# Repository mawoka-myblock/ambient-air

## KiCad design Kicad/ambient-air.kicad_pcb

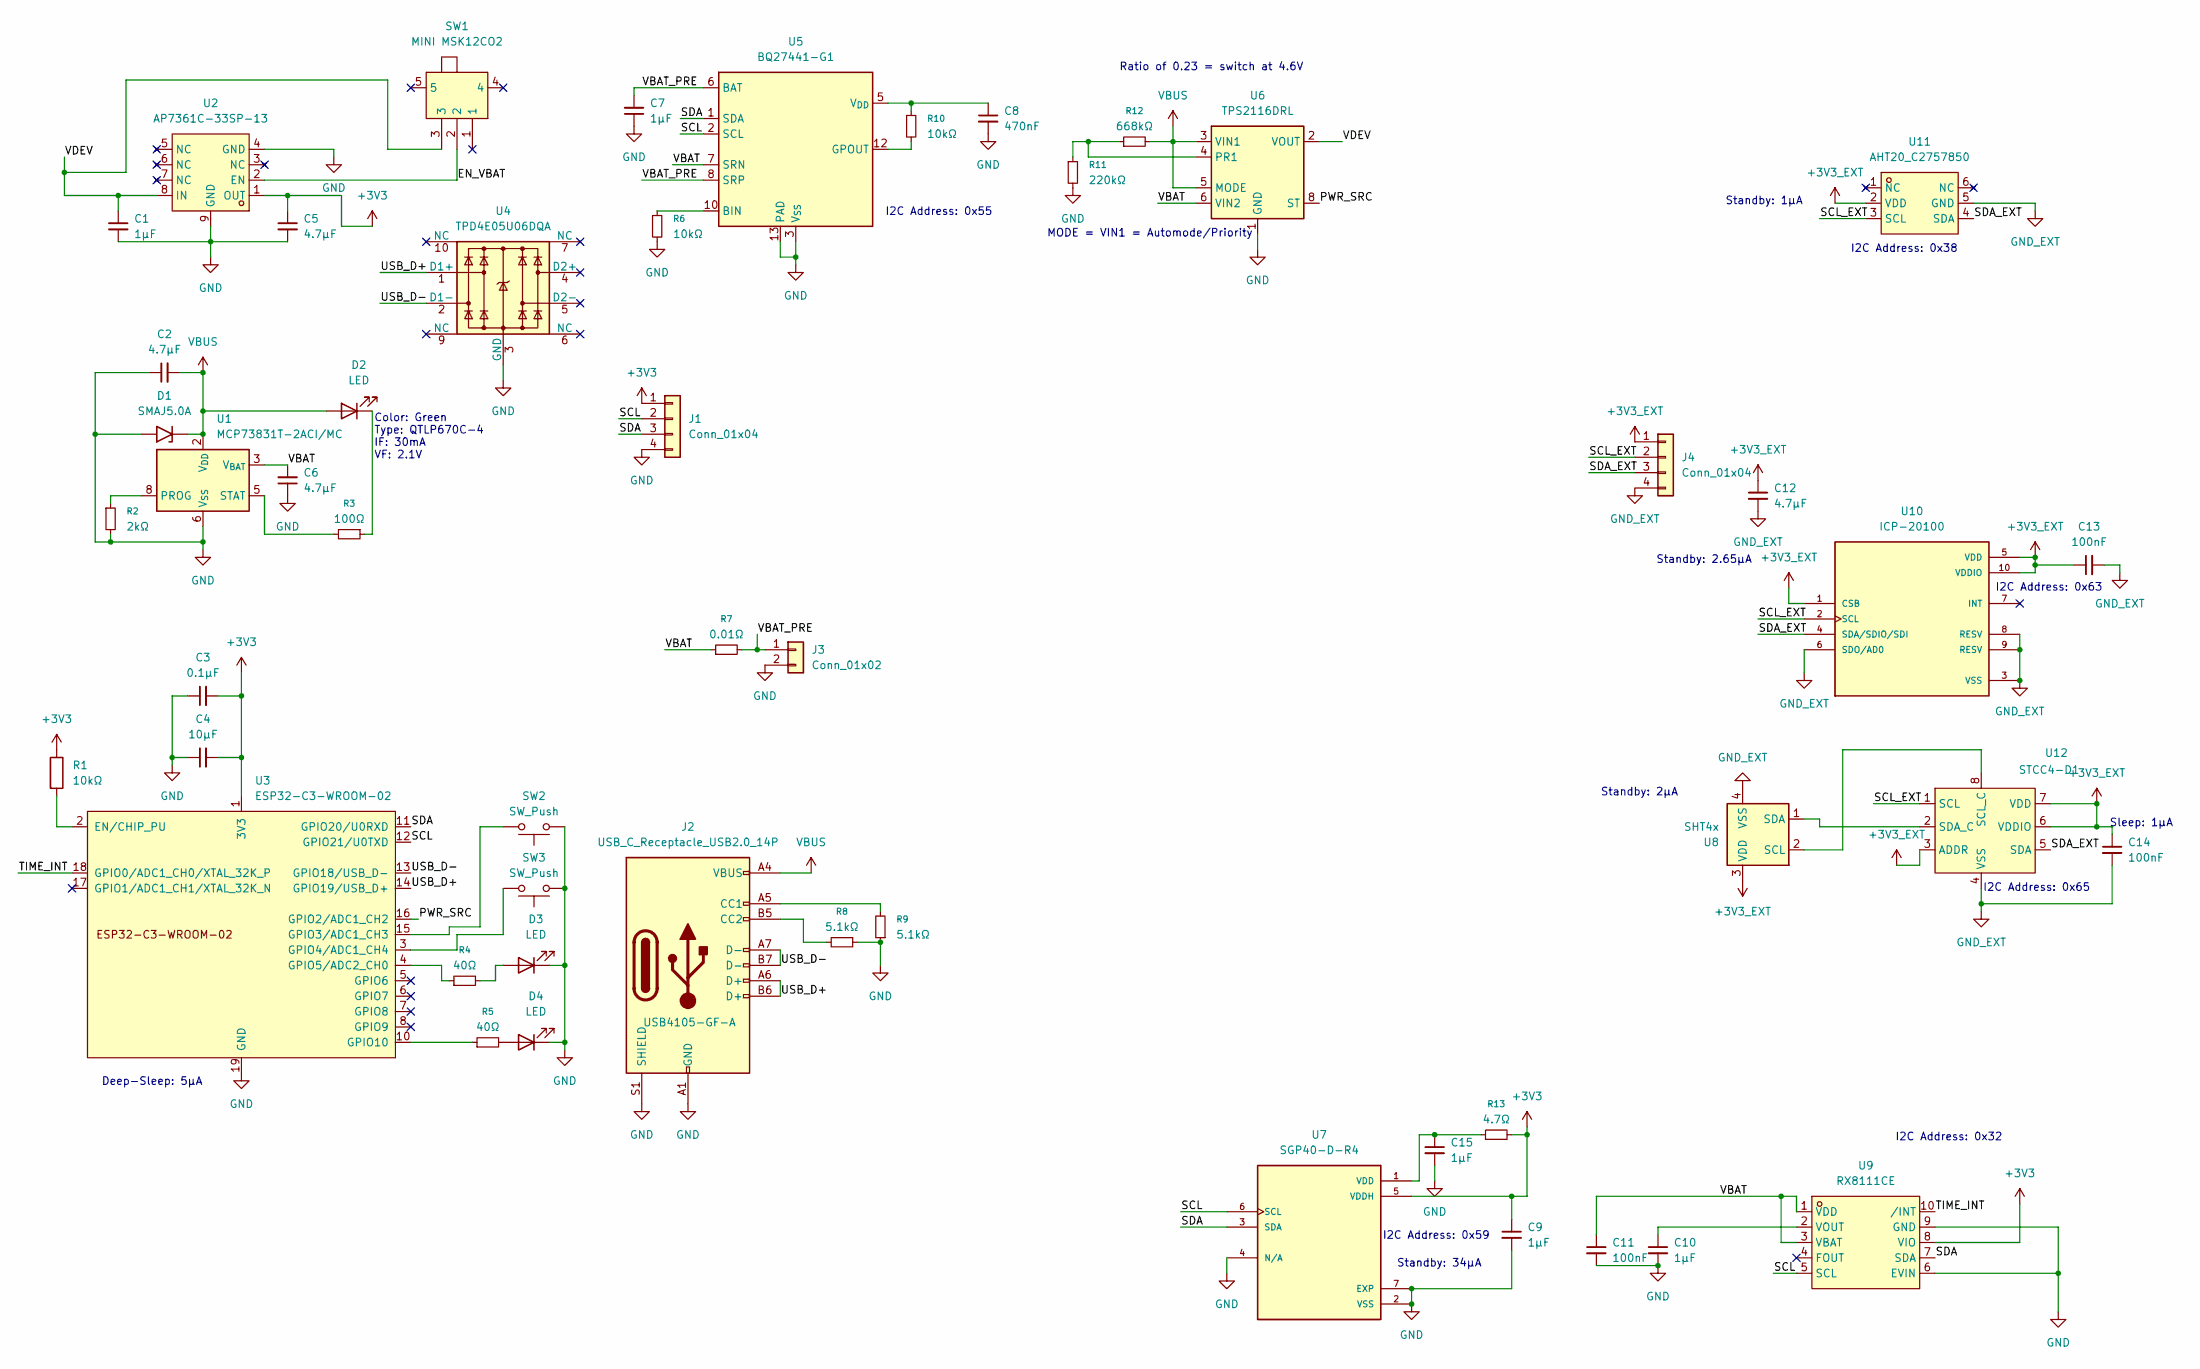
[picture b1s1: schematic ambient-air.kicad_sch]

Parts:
C1, C7, C9, C10, C15: 1µF; C_0603_1608Metric
C2, C5, C6, C12: 4.7µF; C_0805_2012Metric
C3: 0.1µF; C_0805_2012Metric
C4: 10µF; C_0805_2012Metric
C8: 470nF; C_0805_2012Metric
C11, C13, C14: 100nF; C_0805_2012Metric
D1: SMAJ5.0A; D_SMA
D2, D3, D4: LED; CP_EIA-3528-12_Kemet-T
J1, J4: Conn_01x04; JST_SH_SM04B-SRSS-TB_1x04-1MP_P1.00mm_Horizontal
J2: USB_C_Receptacle_USB2.0_14P; USB_C_Receptacle_GCT_USB4105-xx-A_16P_TopMnt_Horizontal
J3: Conn_01x02; JST_PH_S2B-PH-SM4-TB_1x02-1MP_P2.00mm_Horizontal
R1, R6, R10: 10kΩ; R_0805_2012Metric
R2: 2kΩ; R_0805_2012Metric
R3: 100Ω; R_0603_1608Metric
R4, R5: 40Ω; R_0603_1608Metric
R7: 0.01Ω; R_0805_2012Metric
R8, R9: 5.1kΩ; R_0805_2012Metric
R11: 220kΩ; R_0603_1608Metric
R12: 668kΩ; R_0603_1608Metric
R13: 4.7Ω; R_0603_1608Metric
SW1: MINI MSK12CO2; SW-SMD_MSK12CO2; LCSC Part C2681570
SW2, SW3: SW_Push; SW-SMD_L6.0-W3.5-LS8.2
U1: MCP73831T-2ACI/MC; DFN-8-1EP_3x2mm_P0.5mm_EP1.7x1.4mm
U2: AP7361C-33SP-13; ESOP-8_L4.9-W3.9-P1.27-LS6.0-BL-EP; LCSC Part C4943338
U3: ESP32-C3-WROOM-02
U4: TPD4E05U06DQA; USON-10_2.5x1.0mm_P0.5mm
U5: BQ27441-G1; Texas_S-PDSO-N12
U6: TPS2116DRL; SOT-583-8
U7: SGP40-D-R4; XCDR_SGP40-D-R4; PARTREV 1.2
U8: SHT4x; Sensirion_DFN-4_1.5x1.5mm_P0.8mm_SHT4x_NoCentralPad
U9: RX8111CE; OSC-SMD_10P-L3.2-W2.5-BL-1; MPN RX8111CE B; LCSC Part C2929261
U10: ICP-20100; PQFN50P200X200X85-10N; PARTREV 1.1
U11: AHT20_C2757850; SENSOR-SMD_L3.0-W3.0-P1.00-BR; LCSC Part C2757850
U12: STCC4-D1; STCC4DR3

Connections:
+3V3: C3.2, C4.2, C5.1, C9.1, J1.1, R1.1, R13.2, U2.1 (OUT), U3.1 (3V3), U7.5 (VDDH), U9.8 (VIO)
+3V3_EXT: C12.1, C13.1, C14.1, J4.1, U8.3 (VDD), U10.1 (CSB), U10.5 (VDD), U10.10 (VDDIO), U11.2 (VDD), U12.3 (ADDR), U12.6 (VDDIO), U12.7 (VDD)
/EN_VBAT: SW1.2, U2.2 (EN)
/PWR_SRC: U3.16 (GPIO2/ADC1_CH2), U6.8 (ST)
/SCL: J1.2, U3.12 (GPIO21/U0TXD), U5.2 (SCL), U7.6 (SCL), U9.5 (SCL)
/SCL_EXT: J4.2, U10.2 (SCL), U11.3 (SCL), U12.1 (SCL)
/SDA: J1.3, U3.11 (GPIO20/U0RXD), U5.1 (SDA), U7.3 (SDA), U9.7 (SDA)
/SDA_EXT: J4.3, U10.4 (SDA/SDIO/SDI), U11.4 (SDA), U12.5 (SDA)
/TIME_INT: U3.18 (GPIO0/ADC1_CH0/XTAL_32K_P), U9.10 (/INT)
/USB_D+: J2.A6 (D+), J2.B6 (D+), U3.14 (GPIO19/USB_D+), U4.1 (D1+)
/USB_D-: J2.A7 (D-), J2.B7 (D-), U3.13 (GPIO18/USB_D-), U4.2 (D1-)
/VBAT: C6.2, C11.1, R7.1, U1.3 (V_{BAT}), U1.4 (V_{BAT}), U5.7 (SRN), U6.6 (VIN2), U9.1 (VDD), U9.3 (VBAT)
/VBAT_PRE: C7.2, J3.1, R7.2, U5.6 (BAT), U5.8 (SRP)
/VDEV: C1.1, SW1.3, U2.8 (IN), U6.2 (VOUT), U6.7 (VOUT)
GND: C1.2, C2.1, C3.1, C4.1, C5.2, C6.1, C7.1, C8.2, C9.2, C10.2, C11.2, C15.2, D1.2 (A2), D3.1 (K), D4.1 (K), J1.4, J2.A1 (GND), J2.A12 (GND), J2.B1 (GND), J2.B12 (GND), J2.S1 (SHIELD), J3.2, R2.2, R6.2, R8.1, R9.1, R11.2, SW2.1, SW3.1, U1.6 (V_{SS}), U2.4 (GND), U2.9 (GND), U3.9 (GND), U3.19 (GND), U4.3 (GND), U4.8 (GND), U5.3 (V_{SS}), U5.13 (PAD), U6.1 (GND), U7.2 (VSS), U7.4 (N/A), U7.7 (EXP), U9.6 (EVIN), U9.9 (GND)
GND_EXT: C12.2, C13.2, C14.2, J4.4, U8.4 (VSS), U10.3 (VSS), U10.6 (SDO/AD0), U10.8 (RESV), U10.9 (RESV), U11.5 (GND), U12.4 (VSS)
unnamed: D2.1 (K), R3.1
unnamed: D3.2 (A), R4.2
unnamed: D4.2 (A), R5.2
unnamed: J2.A5 (CC1), R9.2
unnamed: J2.B5 (CC2), R8.2
unnamed: R2.1, U1.8 (PROG)
unnamed: R3.2, U1.5 (STAT)
unnamed: R1.2, U3.2 (EN/CHIP_PU)
unnamed: SW2.2, U3.15 (GPIO3/ADC1_CH3)
unnamed: SW3.2, U3.3 (GPIO4/ADC1_CH4)
unnamed: R4.1, U3.4 (GPIO5/ADC2_CH0)
unnamed: R5.1, U3.10 (GPIO10)
unnamed: R6.1, U5.10 (BIN)
unnamed: R10.2, U5.12 (GPOUT)
unnamed: C8.1, R10.1, U5.5 (V_{DD})
unnamed: R11.1, R12.1, U6.4 (PR1)
unnamed: C15.1, R13.1, U7.1 (VDD)
unnamed: C10.1, U9.2 (VOUT)
unnamed: U8.2 (SCL), U12.8 (SCL_C)
unnamed: U8.1 (SDA), U12.2 (SDA_C)
VBUS: C2.2, D1.1 (A1), D2.2 (A), J2.A4 (VBUS), J2.A9 (VBUS), J2.B4 (VBUS), J2.B9 (VBUS), R12.2, U1.1 (V_{DD}), U1.2 (V_{DD}), U6.3 (VIN1), U6.5 (MODE)

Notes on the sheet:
Deep-Sleep: 5µA
Ratio of 0.23 = switch at 4.6V
MODE = VIN1 = Automode/Priority
Standby: 34µA
I2C Address: 0x63
Standby: 1µA
I2C Address: 0x32
I2C Address: 0x38
Color: Green Type: QTLP670C-4 IF: 30mA VF: 2.1V
Standby: 2.65µA
I2C Address: 0x59
Sleep: 1µA
I2C Address: 0x65
I2C Address: 0x55
Standby: 2µA

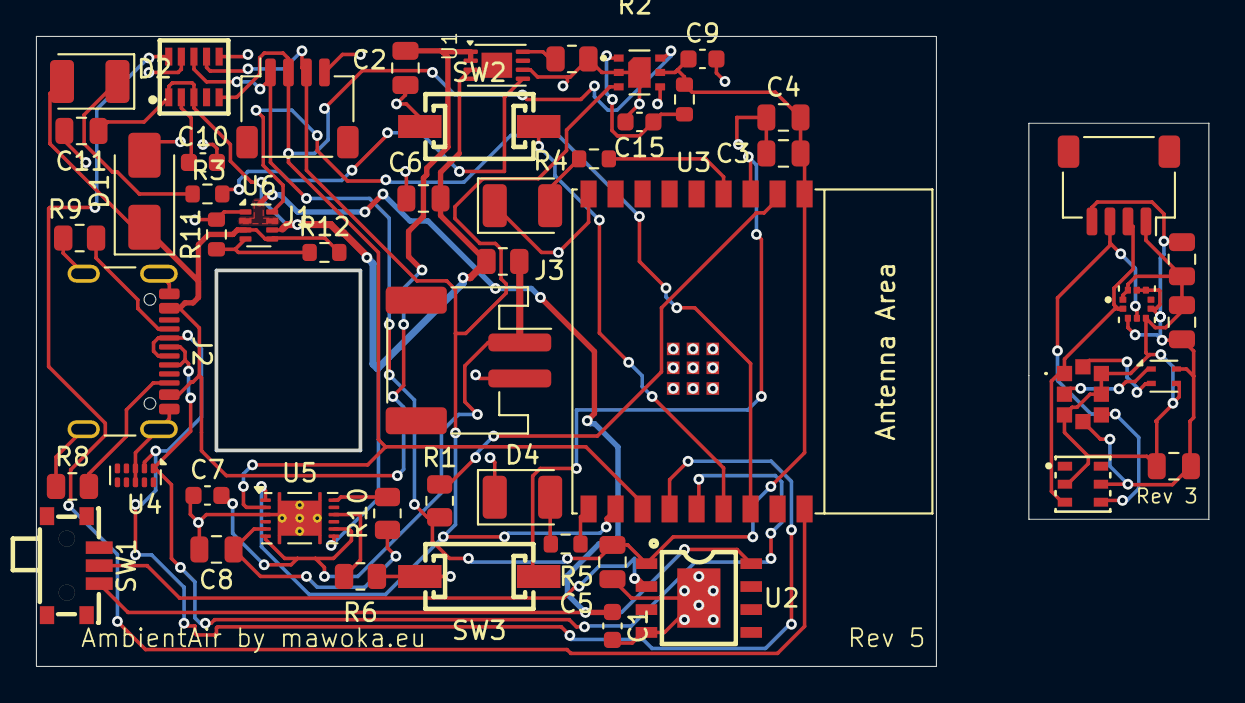
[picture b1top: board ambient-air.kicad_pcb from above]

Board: 2 copper layers, 50.0 x 35.0 mm, 53 parts (0 on the bottom side), 37 nets.

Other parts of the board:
B1, B2: Board

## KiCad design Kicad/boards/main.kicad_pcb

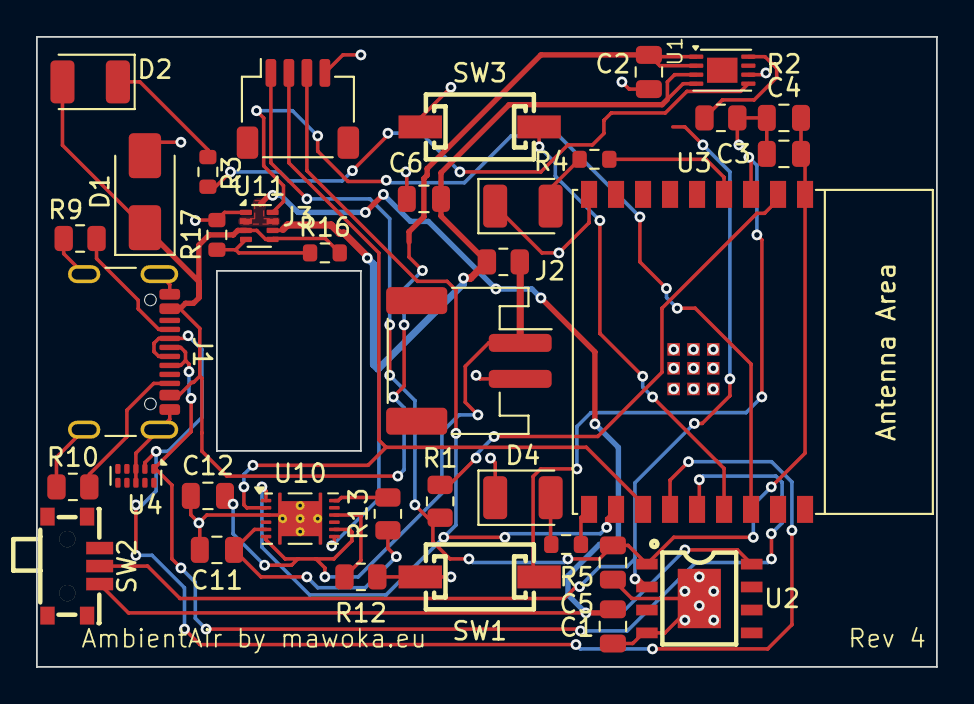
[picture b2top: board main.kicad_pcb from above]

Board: 2 copper layers, 50.0 x 35.0 mm, 37 parts (0 on the bottom side), 28 nets.

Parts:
B1: Board
C1, C12: 1µF; C_0805_2012Metric
C2, C5, C6: 4.7µF; C_0805_2012Metric
C3: 0.1µF; C_0805_2012Metric
C4: 10µF; C_0805_2012Metric
C11: 470nF; C_0805_2012Metric
D1: SMAJ5.0A; D_SMA
D2, D3, D4: LED; CP_EIA-3528-12_Kemet-T
J1: USB_C_Receptacle_USB2.0_14P; USB_C_Receptacle_GCT_USB4105-xx-A_16P_TopMnt_Horizontal
J2: Conn_01x02; JST_PH_S2B-PH-SM4-TB_1x02-1MP_P2.00mm_Horizontal
J3: Conn_01x04; JST_SH_SM04B-SRSS-TB_1x04-1MP_P1.00mm_Horizontal
R1, R12, R13: 10kΩ; R_0805_2012Metric
R2: 2kΩ; R_0805_2012Metric
R3: 100Ω; R_0603_1608Metric
R4, R5: 40Ω; R_0603_1608Metric
R9, R10: 5.1kΩ; R_0805_2012Metric
R11: 0.01Ω; R_0805_2012Metric
R16: 668kΩ; R_0603_1608Metric
R17: 220kΩ; R_0603_1608Metric
SW1, SW3: SW_Push; SW-SMD_L6.0-W3.5-LS8.2
SW2: MINI MSK12CO2; SW-SMD_MSK12CO2
U1: MCP73831T-2ACI/MC; DFN-8-1EP_3x2mm_P0.5mm_EP1.7x1.4mm
U2: AP7361C-33SP-13; ESOP-8_L4.9-W3.9-P1.27-LS6.0-BL-EP
U3: ESP32-C3-WROOM-02
U4: TPD4E05U06DQA; USON-10_2.5x1.0mm_P0.5mm
U10: BQ27441-G1; Texas_S-PDSO-N12
U11: TPS2116DRL; SOT-583-8

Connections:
+3V3: C3.2, C4.2, C5.1, J3.1, R1.1, U2.1 (OUT), U3.1 (3V3)
/EN_VBAT: SW2.2, U2.2 (EN)
/PWR_SRC: U3.16 (GPIO2/ADC1_CH2), U11.8 (ST)
/SCL: J3.2, U3.12 (GPIO21/U0TXD), U10.2 (SCL)
/SDA: J3.3, U3.11 (GPIO20/U0RXD), U10.1 (SDA)
/USB_D+: J1.A6 (D+), J1.B6 (D+), U3.14 (GPIO19/USB_D+), U4.1 (D1+)
/USB_D-: J1.A7 (D-), J1.B7 (D-), U3.13 (GPIO18/USB_D-), U4.2 (D1-)
/VBAT: C6.2, R11.1, U1.3 (V_{BAT}), U1.4 (V_{BAT}), U10.7 (SRN), U11.6 (VIN2)
/VBAT_PRE: C12.2, J2.1, R11.2, U10.6 (BAT), U10.8 (SRP)
/VDEV: C1.1, SW2.3, U2.8 (IN), U11.2 (VOUT), U11.7 (VOUT)
GND: C1.2, C2.1, C3.1, C4.1, C5.2, C6.1, C11.2, C12.1, D1.2 (A2), D3.1 (K), D4.1 (K), J1.A1 (GND), J1.A12 (GND), J1.B1 (GND), J1.B12 (GND), J1.S1 (SHIELD), J2.2, J3.4, R2.2, R9.1, R10.1, R12.2, R17.2, SW1.1, SW3.1, U1.6 (V_{SS}), U2.4 (GND), U2.9 (GND), U3.9 (GND), U3.19 (GND), U4.3 (GND), U4.8 (GND), U10.3 (V_{SS}), U10.13 (PAD), U11.1 (GND)
unnamed: D2.1 (K), R3.1
unnamed: D3.2 (A), R4.2
unnamed: D4.2 (A), R5.2
unnamed: J1.A5 (CC1), R9.2
unnamed: J1.B5 (CC2), R10.2
unnamed: R2.1, U1.8 (PROG)
unnamed: R3.2, U1.5 (STAT)
unnamed: R1.2, U3.2 (EN/CHIP_PU)
unnamed: SW3.2, U3.15 (GPIO3/ADC1_CH3)
unnamed: SW1.2, U3.3 (GPIO4/ADC1_CH4)
unnamed: R4.1, U3.4 (GPIO5/ADC2_CH0)
unnamed: R5.1, U3.10 (GPIO10)
unnamed: R12.1, U10.10 (BIN)
unnamed: R13.2, U10.12 (GPOUT)
unnamed: C11.1, R13.1, U10.5 (V_{DD})
unnamed: R16.1, R17.1, U11.4 (PR1)
VBUS: C2.2, D1.1 (A1), D2.2 (A), J1.A4 (VBUS), J1.A9 (VBUS), J1.B4 (VBUS), J1.B9 (VBUS), R16.2, U1.1 (V_{DD}), U1.2 (V_{DD}), U11.3 (VIN1), U11.5 (MODE)

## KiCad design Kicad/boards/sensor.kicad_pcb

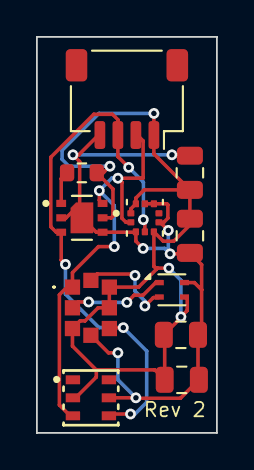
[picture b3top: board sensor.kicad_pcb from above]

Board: 2 copper layers, 10.0 x 22.0 mm, 12 parts (0 on the bottom side), 7 nets.

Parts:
B2: Board
C7, C8: 100nF; C_0805_2012Metric
C9: 1µF; C_0805_2012Metric
C10: 4.7µF; C_0805_2012Metric
J4: Conn_01x04; JST_SH_SM04B-SRSS-TB_1x04-1MP_P1.00mm_Horizontal
R6: 4.7Ω; R_0603_1608Metric
U5: SHT4x; Sensirion_DFN-4_1.5x1.5mm_P0.8mm_SHT4x_NoCentralPad
U6: STCC4-D1; STCC4DR3
U7: AHT20_C2757850; SENSOR-SMD_L3.0-W3.0-P1.00-BR
U8: SGP40-D-R4; XCDR_SGP40-D-R4
U9: ICP-20100; PQFN50P200X200X85-10N

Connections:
+3V3_EXT: C7.1, C8.1, C9.1, C10.1, J4.1, R6.2, U5.3 (VDD), U6.3 (ADDR), U6.6 (VDDIO), U6.7 (VDD), U7.2 (VDD), U8.5 (VDDH), U9.1 (CSB), U9.5 (VDD), U9.10 (VDDIO)
/SCL_EXT: J4.2, U6.1 (SCL), U7.3 (SCL), U8.6 (SCL), U9.2 (SCL)
/SDA_EXT: J4.3, U6.5 (SDA), U7.4 (SDA), U8.3 (SDA), U9.4 (SDA/SDIO/SDI)
GND_EXT: C7.2, C8.2, C9.2, C10.2, J4.4, U5.4 (VSS), U6.4 (VSS), U7.5 (GND), U8.2 (VSS), U8.4 (N/A), U8.7 (EXP), U9.3 (VSS), U9.6 (SDO/AD0), U9.8 (RESV), U9.9 (RESV)
unnamed: U5.2 (SCL), U6.8 (SCL_C)
unnamed: U5.1 (SDA), U6.2 (SDA_C)
unnamed: R6.1, U8.1 (VDD)

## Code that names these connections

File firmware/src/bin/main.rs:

#![no_std]
#![no_main]
#![deny(
    clippy::mem_forget,
    reason = "mem::forget is generally not safe to do with esp_hal types, especially those \
    holding buffers for the duration of a data transfer."
)]

use embassy_executor::Spawner;
use embassy_sync::blocking_mutex::raw::NoopRawMutex;
use embassy_sync::mutex::Mutex;
use embassy_time::Timer;
use esp_hal::Async;
use esp_hal::clock::CpuClock;
use esp_hal::i2c::master::{self as I2C, I2c};
use esp_hal::ledc::timer::TimerIFace;
use esp_hal::ledc::{Ledc, LowSpeed, timer};
use esp_hal::rtc_cntl::wakeup_cause;
use esp_hal::system::SleepSource;
use esp_hal::time::Rate;
use esp_hal::timer::timg::TimerGroup;
// use esp_hal::tsens::{self, TemperatureSensor};
use esp_radio::ble::controller::BleConnector;
use firmware::bluetooth::run_bt;
use firmware::button::button_task;
use firmware::data::Devices;
use firmware::energy::set_sgp40;
use firmware::leds::{Leds, led_task};
use firmware::measurements::lp::lp_measurement;
use firmware::measurements::measure;
use firmware::measurements::sampling::{move_to_nvs, record_sample};
use firmware::measurements::voc::restore_voc_state;
use firmware::storage::Nvs;
use firmware::tasks::battery;
use firmware::tasks::{settings, sleep, stcc4};
use firmware::{COMMAND_CHANNEL, Commands, PowerState};
use trouble_host::prelude::ExternalController;
use {esp_backtrace as _, esp_println as _};

extern crate alloc;
esp_bootloader_esp_idf::esp_app_desc!();

#[esp_rtos::main]
async fn main(spawner: Spawner) {
    let wakeup_cause_var = wakeup_cause();
    if wakeup_cause_var as i8 == SleepSource::Gpio as i8 {
        unsafe { firmware::POWER_STATE = PowerState::BluetoothMode as i8 }
    }

    // Set CPU frequency to try to save as much power as possible
    let config = esp_hal::Config::default().with_cpu_clock(
        match PowerState::try_from(unsafe { firmware::POWER_STATE })
            .unwrap_or(PowerState::SampleMode)
        {
            PowerState::DeepSleep => CpuClock::_80MHz,
            PowerState::BluetoothMode => CpuClock::_160MHz,
            PowerState::SampleMode => CpuClock::_80MHz, // _80MHz
            PowerState::SensorActiveSleep => CpuClock::_80MHz,
        },
    );

    // -----------------
    // Init peripherals and rtos
    // -----------------
    let peripherals = esp_hal::init(config);
    esp_alloc::heap_allocator!(size: 64 * 1024);
    let timg0 = TimerGroup::new(peripherals.TIMG0);
    let sw_interrupt =
        esp_hal::interrupt::software::SoftwareInterruptControl::new(peripherals.SW_INTERRUPT);
    esp_rtos::start(timg0.timer0, sw_interrupt.software_interrupt0);
    let beginning = embassy_time::Instant::now();

    // -----------------
    // Init the NVS storage (tickv)
    // -----------------
    let raw_nvs = Nvs::new(firmware::NVS_OFFSET, firmware::NVS_SIZE, peripherals.FLASH).unwrap();
    let nvs = Mutex::new(raw_nvs);

    // -----------------
    // Init I2C
    // -----------------
    let i2c_hal = I2C::I2c::new(
        peripherals.I2C0,
        I2C::Config::default().with_frequency(Rate::from_khz(100)),
    )
    .unwrap()
    .with_sda(peripherals.GPIO20)
    .with_scl(peripherals.GPIO21)
    .into_async();
    let i2c_bus =
        &*firmware::mk_static!(Mutex<NoopRawMutex, I2c<'static, Async>>, Mutex::new(i2c_hal));

    let devices = firmware::mk_static!(Devices<'static>, Devices::init(i2c_bus, nvs).await);

    // -----------------
    // Restore SGP40 algo data
    // -----------------
    let restored_voc_state = restore_voc_state();
    if restored_voc_state.uptime > 0.0 {
        devices
            .sgp40
            .lock()
            .await
            .set_algorithm_state(&restored_voc_state);
    }

    // -----------------
    // Run LP measurement
    // -----------------
    if unsafe { firmware::POWER_STATE == PowerState::SensorActiveSleep as i8 } {
        lp_measurement(devices, peripherals.LPWR).await;
    }

    // -----------------
    // Run sample mode fn
    // -----------------
    if unsafe { firmware::POWER_STATE == PowerState::SampleMode as i8 } {
        record_sample(devices, beginning).await;
    }

    set_sgp40(devices).await;

    // -----------------
    // Save sample if that is needed
    // -----------------
    if unsafe { firmware::NEEDS_SAMPLES_WRITTEN_TO_NVS == 1 } {
        let mut nvs_l = devices.nvs.lock().await;
        move_to_nvs(&mut nvs_l).await;
        unsafe { firmware::NEEDS_SAMPLES_WRITTEN_TO_NVS = 0 };
    }

    // -----------------
    // Init LED peripherals and struct
    // -----------------
    let ledc = firmware::mk_static!(Ledc<'static>, Ledc::new(peripherals.LEDC));
    ledc.set_global_slow_clock(esp_hal::ledc::LSGlobalClkSource::APBClk);
    let lstimer0: &'static mut timer::Timer<'static, LowSpeed> = firmware::mk_static!(
        timer::Timer<'static, LowSpeed>,
        ledc.timer::<LowSpeed>(timer::Number::Timer2)
    );
    lstimer0
        .configure(timer::config::Config {
            duty: timer::config::Duty::Duty10Bit,
            clock_source: timer::LSClockSource::APBClk,
            frequency: Rate::from_khz(24),
        })
        .unwrap();
    let leds: &'static mut Leds<'static> = firmware::mk_static!(
        Leds<'static>,
        Leds::new(ledc, lstimer0, peripherals.GPIO5, peripherals.GPIO10)
    );

    // -----------------
    // Spawn main tasks
    // -----------------
    spawner.spawn(led_task(leds).unwrap());
    spawner.spawn(measure(devices).unwrap());
    spawner.spawn(button_task(peripherals.GPIO3, peripherals.GPIO4).unwrap());
    spawner.spawn(sleep::sleep_task(devices, peripherals.LPWR).unwrap());
    spawner.spawn(settings::settings_task().unwrap());
    spawner.spawn(stcc4::stcc4_task(devices).unwrap());
    spawner.spawn(battery::auto_sleep().unwrap());

    // Deep sleep for 1 year if battery is super low
    battery::deep_sleep_forever_on_low_battery(devices).await;

    // -----------------
    // Init Bluetooth
    // -----------------
    let connector = BleConnector::new(peripherals.BT, Default::default()).unwrap();
    let controller: ExternalController<_, 20> = ExternalController::new(connector);

    spawner.spawn(run_bt(controller, devices).unwrap());

    // -----------------
    // Main loop breathing led
    // -----------------
    battery::show_battery_percentage().await;

    loop {
        Timer::after_millis(1500).await;
        COMMAND_CHANNEL
            .immediate_publisher()
            .publish_immediate(Commands::Led(firmware::leds::LedCommand::Set {
                led: 1,
                level: 100,
            }));
        Timer::after_millis(20).await;
        COMMAND_CHANNEL
            .immediate_publisher()
            .publish_immediate(Commands::Led(firmware::leds::LedCommand::Set {
                led: 1,
                level: 0,
            }));
    }
}

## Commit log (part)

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2025-11-18 Quicksave
2025-11-18 iBom
2025-12-01 Separated PCBs
2025-12-01 Battery fuel gauge
2025-12-14 Progress, saving data to storage
2025-12-27 Quick save
2026-01-19 Progress
2026-02-11 auto svelte adapter
2026-02-20 Bump svelte from 5.47.0 to 5.51.5 in /website
    Bumps [svelte](https://github.com/sveltejs/svelte/tree/HEAD/packages/svelte) from 5.47.0 to 5.51.5.
    - [Release notes](https://github.com/sveltejs/svelte/releases)
    - [Changelog](https://github.com/sveltejs/svelte/blob/main/packages/svelte/CHANGELOG.md)
    - [Commits](https://github.com/sveltejs/svelte/commits/svelte@5.51.5/packages/svelte)
    ---
    updated-dependencies:
2026-02-20 Bump @sveltejs/kit from 2.50.0 to 2.52.2 in /website
    Bumps [@sveltejs/kit](https://github.com/sveltejs/kit/tree/HEAD/packages/kit) from 2.50.0 to 2.52.2.
    - [Release notes](https://github.com/sveltejs/kit/releases)
    - [Changelog](https://github.com/sveltejs/kit/blob/main/packages/kit/CHANGELOG.md)
    - [Commits](https://github.com/sveltejs/kit/commits/@sveltejs/kit@2.52.2/packages/kit)
    ---
    updated-dependencies:
2026-02-28 Bump svelte from 5.47.0 to 5.53.5 in /website
    Bumps [svelte](https://github.com/sveltejs/svelte/tree/HEAD/packages/svelte) from 5.47.0 to 5.53.5.
    - [Release notes](https://github.com/sveltejs/svelte/releases)
    - [Changelog](https://github.com/sveltejs/svelte/blob/main/packages/svelte/CHANGELOG.md)
    - [Commits](https://github.com/sveltejs/svelte/commits/svelte@5.53.5/packages/svelte)
    ---
    updated-dependencies:
2026-03-02 Bump @sveltejs/kit from 2.50.0 to 2.53.3 in /website
    Bumps [@sveltejs/kit](https://github.com/sveltejs/kit/tree/HEAD/packages/kit) from 2.50.0 to 2.53.3.
    - [Release notes](https://github.com/sveltejs/kit/releases)
    - [Changelog](https://github.com/sveltejs/kit/blob/main/packages/kit/CHANGELOG.md)
    - [Commits](https://github.com/sveltejs/kit/commits/@sveltejs/kit@2.53.3/packages/kit)
    ---
    updated-dependencies:
2026-04-06 Bump vite from 7.3.1 to 7.3.2 in /website
    Bumps [vite](https://github.com/vitejs/vite/tree/HEAD/packages/vite) from 7.3.1 to 7.3.2.
    - [Release notes](https://github.com/vitejs/vite/releases)
    - [Changelog](https://github.com/vitejs/vite/blob/v7.3.2/packages/vite/CHANGELOG.md)
    - [Commits](https://github.com/vitejs/vite/commits/v7.3.2/packages/vite)
    ---
    updated-dependencies:
2026-04-10 Bump @sveltejs/kit from 2.50.0 to 2.57.1 in /website
    Bumps [@sveltejs/kit](https://github.com/sveltejs/kit/tree/HEAD/packages/kit) from 2.50.0 to 2.57.1.
    - [Release notes](https://github.com/sveltejs/kit/releases)
    - [Changelog](https://github.com/sveltejs/kit/blob/main/packages/kit/CHANGELOG.md)
    - [Commits](https://github.com/sveltejs/kit/commits/@sveltejs/kit@2.57.1/packages/kit)
    ---
    updated-dependencies:
2026-05-10 Get basic sampling working
2026-05-10 Don't send too many notifications
2026-05-11 Before updating deps
2026-05-11 Move from state to channel and signal
2026-05-11 Fix clippy issues
2026-05-12 Add some battery monitoring and more refactoring
2026-05-13 Reduce size for samples and nvs
2026-05-14 Fix sampling and add timestamps to samples
2026-05-14 Add timestamps to web ui
2026-05-14 Progress, further investigation for rtc needed
2026-05-18 Add: - Central sensor init for Devices - Co2 task for stcc4 reset and preconditioning - General reset and precon handling for stcc4 - time with only time_since_boot
2026-05-21 Bump @sveltejs/kit from 2.50.0 to 2.60.1 in /website
    Bumps [@sveltejs/kit](https://github.com/sveltejs/kit/tree/HEAD/packages/kit) from 2.50.0 to 2.60.1.
    - [Release notes](https://github.com/sveltejs/kit/releases)
    - [Changelog](https://github.com/sveltejs/kit/blob/main/packages/kit/CHANGELOG.md)
    - [Commits](https://github.com/sveltejs/kit/commits/@sveltejs/kit@2.60.1/packages/kit)
    ---
    updated-dependencies:
2026-05-27 add graph to ui
2026-05-27 Bump svelte from 5.47.0 to 5.55.7 in /website
    Bumps [svelte](https://github.com/sveltejs/svelte/tree/HEAD/packages/svelte) from 5.47.0 to 5.55.7.
    - [Release notes](https://github.com/sveltejs/svelte/releases)
    - [Changelog](https://github.com/sveltejs/svelte/blob/main/packages/svelte/CHANGELOG.md)
    - [Commits](https://github.com/sveltejs/svelte/commits/svelte@5.55.7/packages/svelte)
    ---
    updated-dependencies:
2026-06-19 Bump vite from 7.3.1 to 7.3.5 in /website
    Bumps [vite](https://github.com/vitejs/vite/tree/HEAD/packages/vite) from 7.3.1 to 7.3.5.
    - [Release notes](https://github.com/vitejs/vite/releases)
    - [Changelog](https://github.com/vitejs/vite/blob/v7.3.5/packages/vite/CHANGELOG.md)
    - [Commits](https://github.com/vitejs/vite/commits/v7.3.5/packages/vite)
    ---
    updated-dependencies:
